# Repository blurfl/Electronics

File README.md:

Maslow PCBs
======================

The TLE5206 offers over-temperature and over-current detection and protection.

This design brings:
- separate controller chip for each motor
- board-mounted heat sinks
- thru-hole parts to aid hand assembly and repair
- mounting holes to match the Arduino Mega2560
- AUX pins on extended end of board
- 4 digital AUX pins
- 2 analog/digital AUX pins
- 3 PWM-capable AUX pins 
- board version ID pins avoids using SPI pins

Layout

Schematic

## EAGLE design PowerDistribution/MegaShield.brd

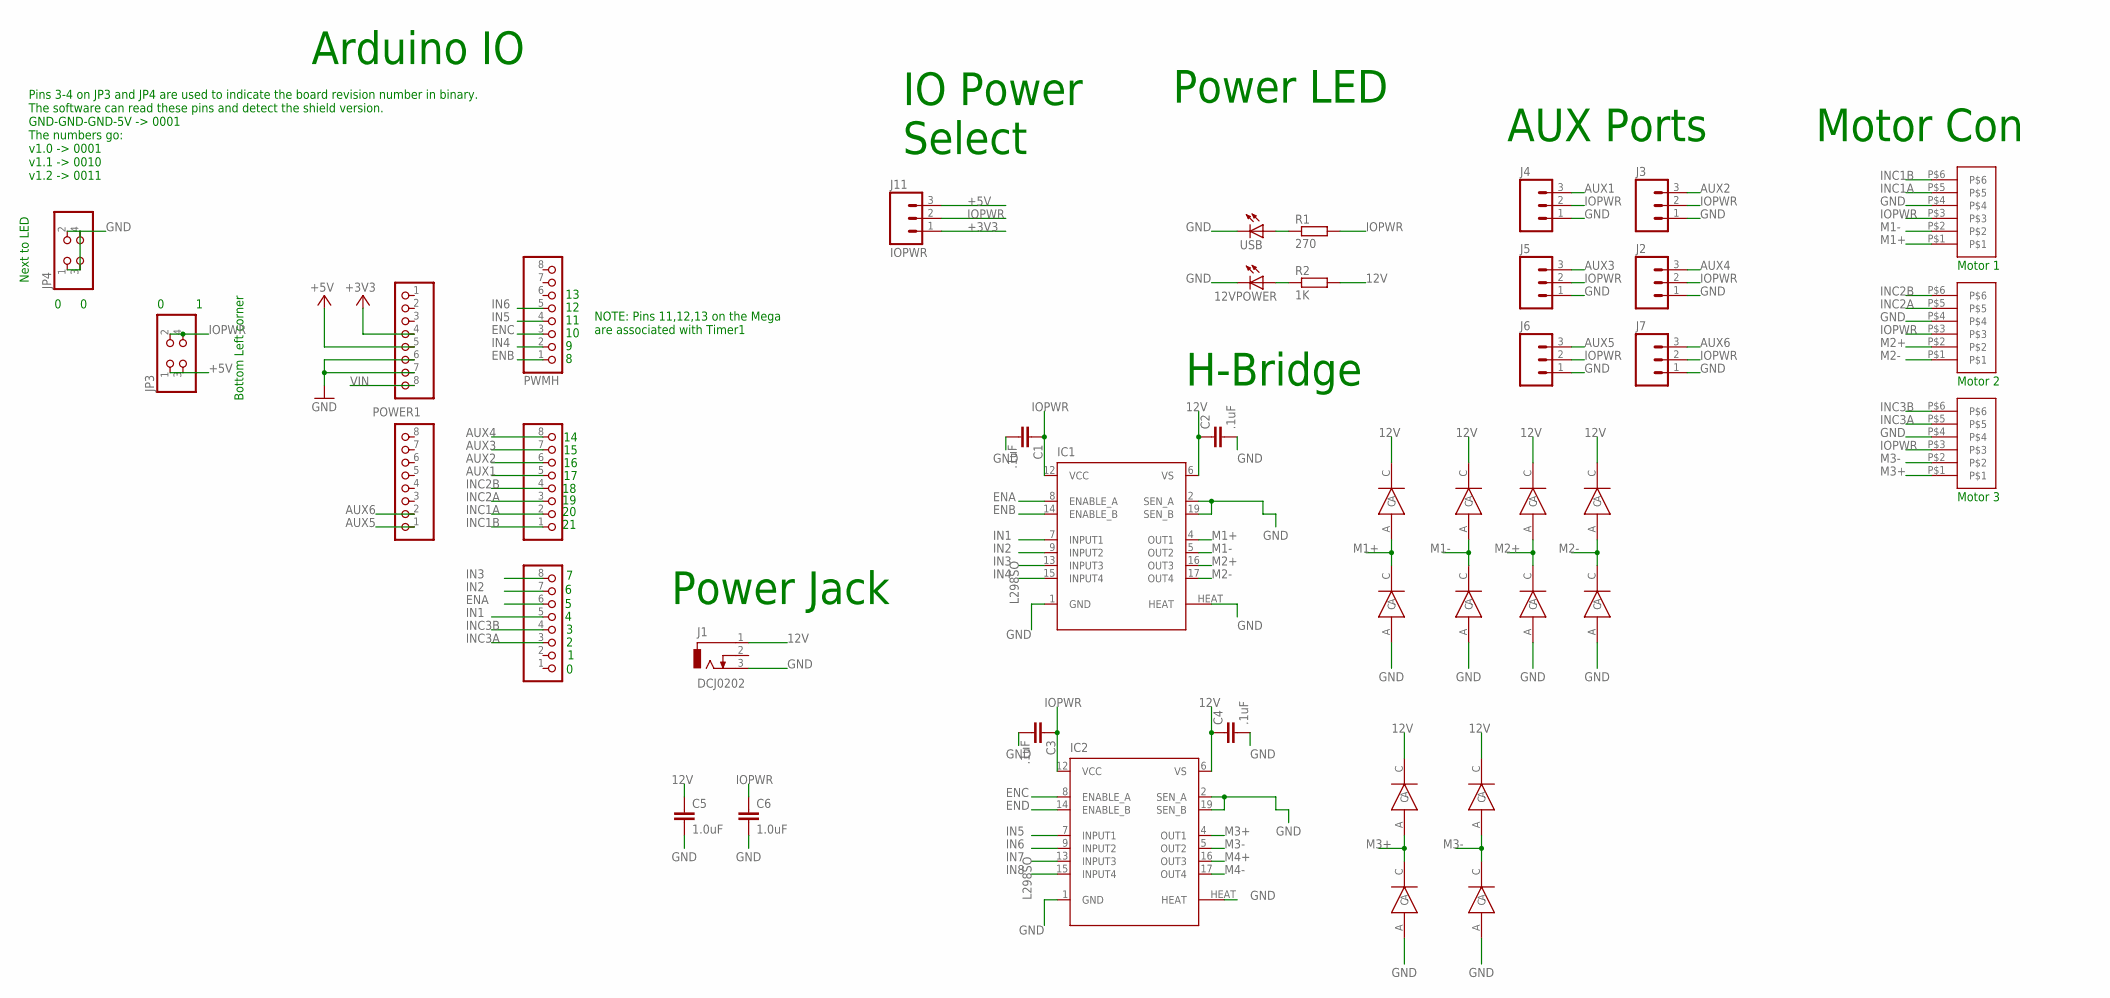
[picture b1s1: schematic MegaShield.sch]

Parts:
12VPOWER: LED_E; LED_1206
C1, C2, C3, C4: .1uF; C0805
C5, C6: 1.0uF; 0805-CAP
COMMUNICATION, COMMUNICATION1: PINHD-1X8; 1X08
IC1, IC2: L298SO; POWERSO-20
J1: DCJ0202
J2, J3, J4, J5, J6, J7: M03LOCK; 1X03_LOCK
J11: IOPWR; 1X03_LOCK
JP3, JP4: PINHD-2X2; 2X02
POWER1: 8x1F-H8.5; 1X08
PWMH: PINHD-1X8; 1X08
PWML: PINHD-1X8; 1X08
R1: 270; R0805
R2: 1K; R0805
U$1, U$12, U$20: JST-PH-6; JST-PHR-6-SMD
U$2, U$3, U$4, U$5, U$6, U$7, U$8, U$9, U$10, U$11, U$13, U$14: MRA4004; SMA
USB: LED_E; LED_1206

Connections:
12V: C2.1, C4.1, C5.1, IC1.6 (VS), IC2.6 (VS), J1.1, R2.2, U$2.C, U$3.C, U$5.C, U$7.C, U$9.C, U$13.C
+3V3: J11.1, POWER1.4
+5V: J11.3, JP3.1, JP3.3, POWER1.5
AUX1: COMMUNICATION.5, J4.3
AUX2: COMMUNICATION.6, J3.3
AUX3: COMMUNICATION.7, J5.3
AUX4: COMMUNICATION.8, J2.3
AUX5: COMMUNICATION1.1, J6.3
AUX6: COMMUNICATION1.2, J7.3
ENA: IC1.8 (ENABLE_A), PWML.6
ENB: IC1.14 (ENABLE_B), PWMH.1
ENC: IC2.8 (ENABLE_A), PWMH.3
END: IC2.14 (ENABLE_B)
GND: 12VPOWER.C, C1.2, C2.2, C3.2, C4.2, C5.2, C6.2, IC1.1 (GND), IC1.2 (SEN_A), IC1.19 (SEN_B), IC1.HEAT, IC2.1 (GND), IC2.2 (SEN_A), IC2.19 (SEN_B), IC2.HEAT, J1.3, J2.1, J3.1, J4.1, J5.1, J6.1, J7.1, JP4.1, JP4.2, JP4.3, JP4.4, POWER1.6, POWER1.7, U$1.P$4, U$4.A, U$6.A, U$8.A, U$10.A, U$11.A, U$12.P$4, U$14.A, U$20.P$4, USB.C
IN1: IC1.7 (INPUT1), PWML.5
IN2: IC1.9 (INPUT2), PWML.7
IN3: IC1.13 (INPUT3), PWML.8
IN4: IC1.15 (INPUT4), PWMH.2
IN5: IC2.7 (INPUT1), PWMH.4
IN6: IC2.9 (INPUT2), PWMH.5
IN7: IC2.13 (INPUT3)
IN8: IC2.15 (INPUT4)
INC1A: COMMUNICATION.2, U$1.P$5
INC1B: COMMUNICATION.1, U$1.P$6
INC2A: COMMUNICATION.3, U$12.P$5
INC2B: COMMUNICATION.4, U$12.P$6
INC3A: PWML.3, U$20.P$5
INC3B: PWML.4, U$20.P$6
IOPWR: C1.1, C3.1, C6.1, IC1.12 (VCC), IC2.12 (VCC), J2.2, J3.2, J4.2, J5.2, J6.2, J7.2, J11.2, JP3.2, JP3.4, R1.2, U$1.P$3, U$12.P$3, U$20.P$3
M1+: IC1.4 (OUT1), U$1.P$1, U$3.A, U$4.C
M1-: IC1.5 (OUT2), U$1.P$2, U$5.A, U$6.C
M2+: IC1.16 (OUT3), U$7.A, U$8.C, U$12.P$2
M2-: IC1.17 (OUT4), U$9.A, U$10.C, U$12.P$1
M3+: IC2.4 (OUT1), U$2.A, U$11.C, U$20.P$1
M3-: IC2.5 (OUT2), U$13.A, U$14.C, U$20.P$2
M4+: IC2.16 (OUT3)
M4-: IC2.17 (OUT4)
unnamed: R1.1, USB.A
unnamed: 12VPOWER.A, R2.1
VIN: POWER1.8

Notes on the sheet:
Motor 1
Motor 2
H-Bridge
Power LED
Power Jack
Arduino IO
AUX Ports
Motor Con
Motor 3
Pins 3-4 on JP3 and JP4 are used to indicate the board revision number in binary. The software can read these pins and detect the shield version. GND-GND-GND-5V -> 0001 The numbers go: v1.0 -> 0001 v1.1 -> 0010 v1.2 -> 0011
NOTE: Pins 11,12,13 on the Mega are associated with Timer1
Next to LED
Bottom Left corner
IO Power Select

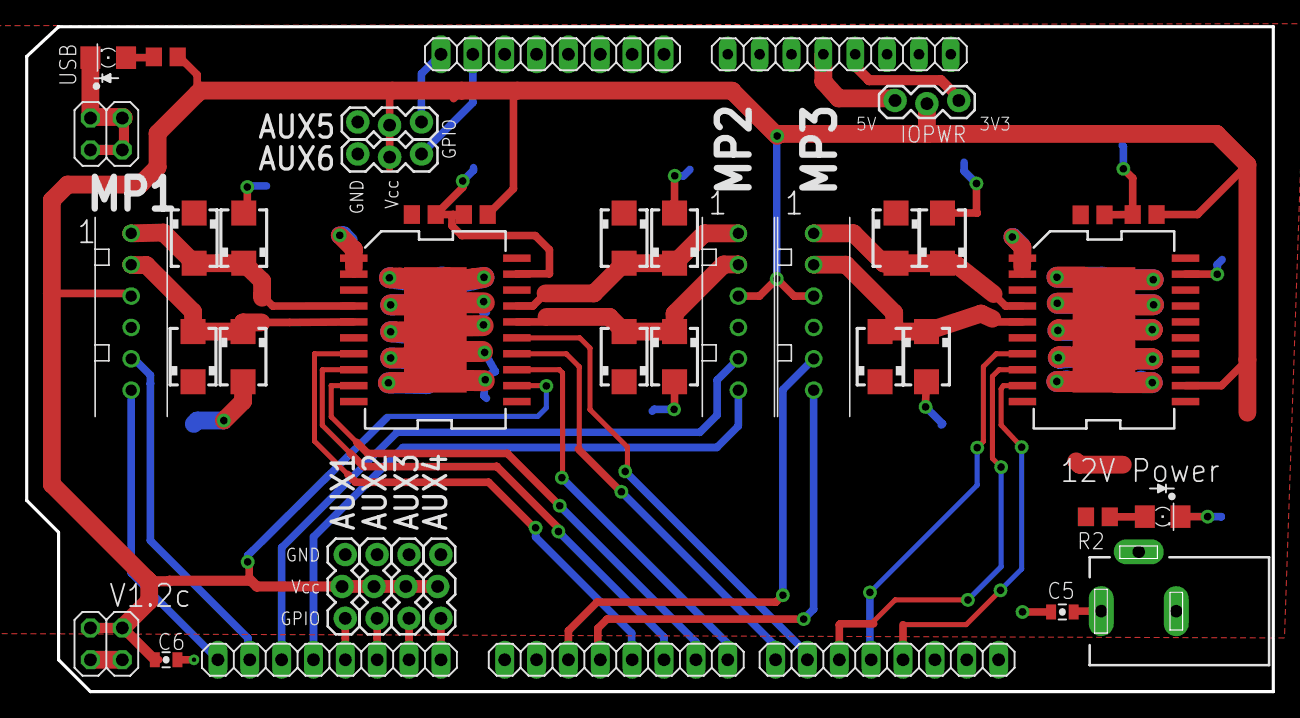
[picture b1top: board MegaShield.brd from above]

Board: 2 copper layers, 99.4 x 53.0 mm, 42 parts (0 on the bottom side), 34 nets.

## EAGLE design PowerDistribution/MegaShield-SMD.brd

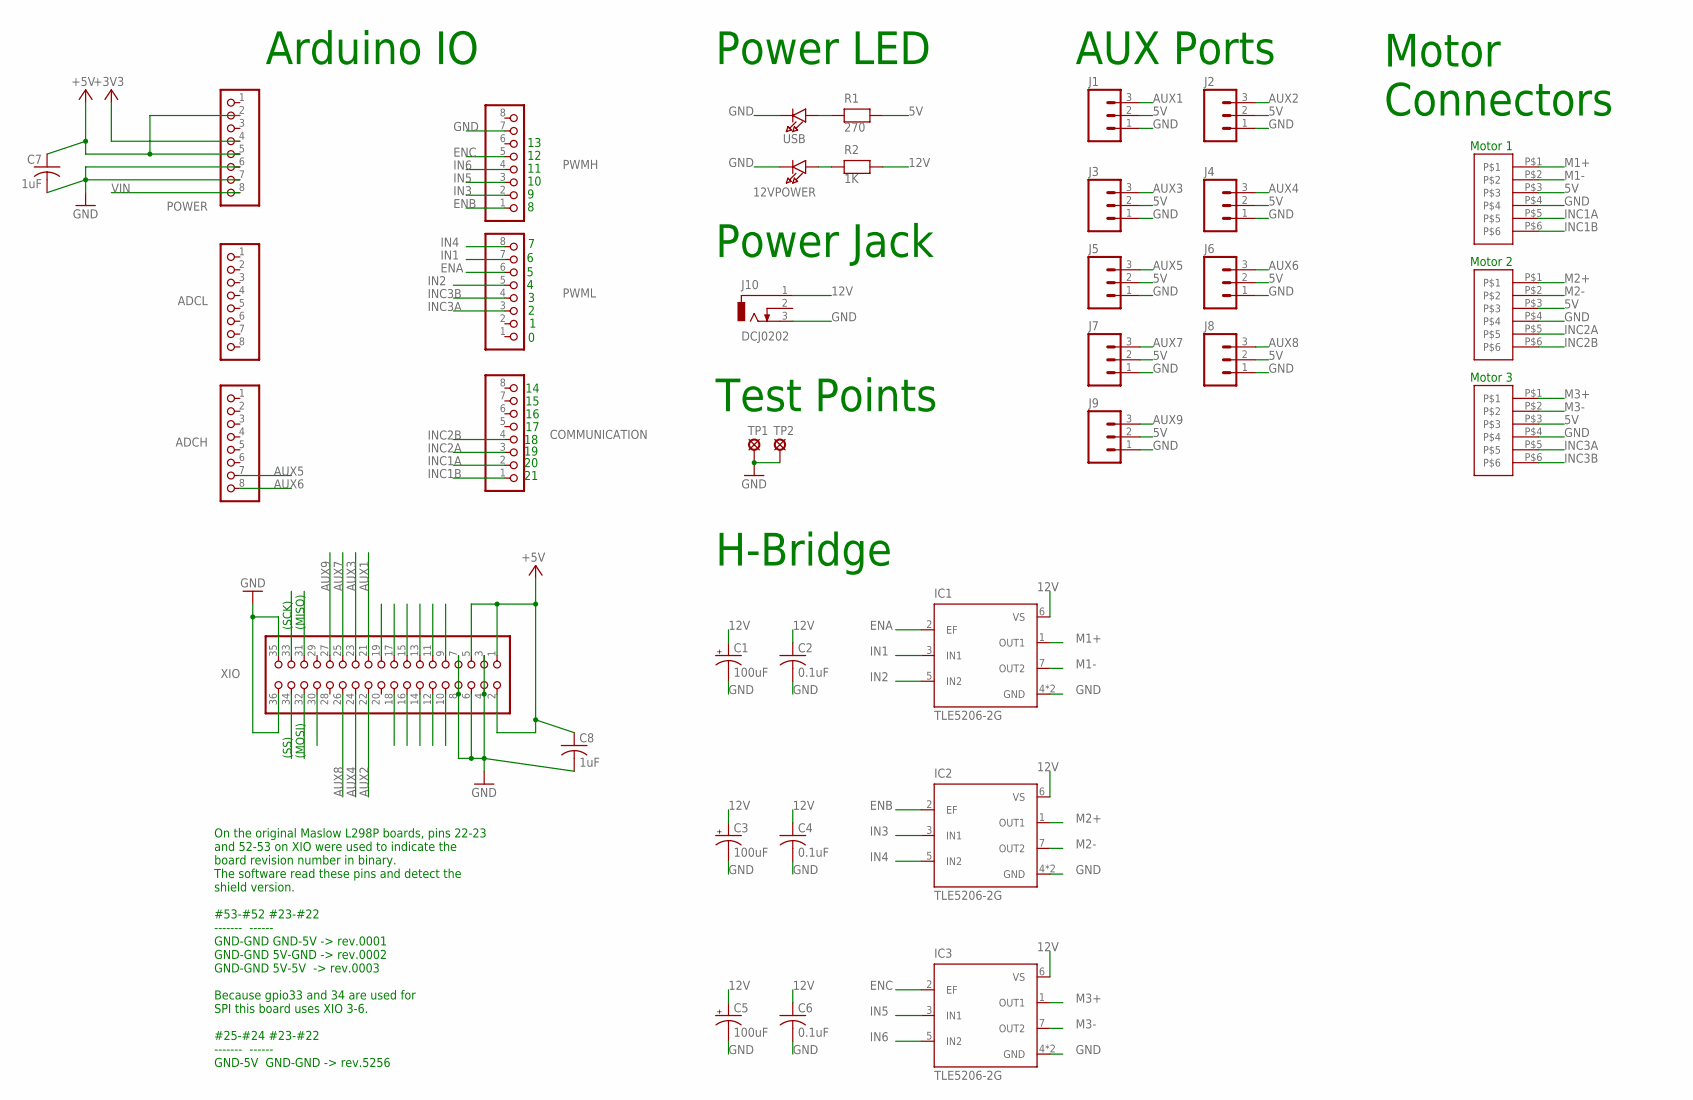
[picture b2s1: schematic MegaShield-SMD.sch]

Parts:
12VPOWER: LED1206; CHIPLED_1206
ADCH: 8x1F-H8.5; 1X08
ADCL: PINHD-1X8; 1X08
C1, C3, C5: 100uF; PANASONIC_E
C2, C4, C6: 0.1uF; C0805K
C7, C8: 1uF; C0805K
COMMUNICATION: PINHD-1X8; 1X08
IC1, IC2: TLE5206-2G; INF-PG-TO263-7-1_L_1PRIMARY
IC3: TLE5206-2G; INF-PG-TO263-7-1_L_1PRIMARY; DIGIKEY TLE5206-2S-ND
J1, J2, J3, J4, J5, J6, J7, J8, J9: M03LOCK; 1X03_LOCK
J10: DCJ0202
MP1, MP2, MP3: JST-PH-6; JST-PHR-6-SMD
POWER: 8x1F-H8.5; 1X08
PWMH: PINHD-1X8; 1X08
PWML: PINHD-1X8; 1X08
R1: 270; 0805
R2: 1K; 0805
TP1, TP2: LSP10
USB: LED1206; CHIPLED_1206
XIO: 18x2F-H8.5; 2X18

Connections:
5V: C7.1, C8.1, J1.2, J2.2, J3.2, J4.2, J5.2, J6.2, J7.2, J8.2, J9.2, MP1.P$3, MP2.P$3, MP3.P$3, POWER.2, POWER.5, R1.2, XIO.1, XIO.2, XIO.5
12V: C1.+, C2.1, C3.+, C4.1, C5.+, C6.1, IC1.6 (VS), IC2.6 (VS), IC3.6 (VS), J10.1, R2.2
+3V3: POWER.4
AUX1: J1.3, XIO.21
AUX2: J2.3, XIO.22
AUX3: J3.3, XIO.23
AUX4: J4.3, XIO.24
AUX5: ADCH.7, J5.3
AUX6: ADCH.8, J6.3
AUX7: J7.3, XIO.25
AUX8: J8.3, XIO.26
AUX9: J9.3, XIO.27
ENA: IC1.2 (EF), PWML.6
ENB: IC2.2 (EF), PWMH.1
ENC: IC3.2 (EF), PWMH.5
GND: 12VPOWER.C, C1.-, C2.2, C3.-, C4.2, C5.-, C6.2, C7.2, C8.2, IC1.4 (GND), IC1.8 (GND), IC2.4 (GND), IC2.8 (GND), IC3.4 (GND), IC3.8 (GND), J1.1, J2.1, J3.1, J4.1, J5.1, J6.1, J7.1, J8.1, J9.1, J10.3, MP1.P$4, MP2.P$4, MP3.P$4, POWER.6, POWER.7, PWMH.7, TP1.MP, TP2.MP, USB.C, XIO.3, XIO.4, XIO.6, XIO.7, XIO.8, XIO.35, XIO.36
IN1: IC1.3 (IN1), PWML.7
IN2: IC1.5 (IN2), PWML.5
IN3: IC2.3 (IN1), PWMH.2
IN4: IC2.5 (IN2), PWML.8
IN5: IC3.3 (IN1), PWMH.3
IN6: IC3.5 (IN2), PWMH.4
INC1A: COMMUNICATION.2, MP1.P$5
INC1B: COMMUNICATION.1, MP1.P$6
INC2A: COMMUNICATION.3, MP2.P$5
INC2B: COMMUNICATION.4, MP2.P$6
INC3A: MP3.P$5, PWML.3
INC3B: MP3.P$6, PWML.4
M1+: IC1.1 (OUT1), MP1.P$1
M1-: IC1.7 (OUT2), MP1.P$2
M2+: IC2.1 (OUT1), MP2.P$1
M2-: IC2.7 (OUT2), MP2.P$2
M3+: IC3.1 (OUT1), MP3.P$1
M3-: IC3.7 (OUT2), MP3.P$2
unnamed: R1.1, USB.A
unnamed: 12VPOWER.A, R2.1
PA6: XIO.9
PA7: XIO.10
PB0: XIO.34
PB1: XIO.33
PB2: XIO.32
PB3: XIO.31
PC0: XIO.18
PC1: XIO.17
PC2: XIO.16
PC3: XIO.15
PC4: XIO.14
PC5: XIO.13
PC6: XIO.12
PC7: XIO.11
PD7: XIO.19
PL0: XIO.30
VIN: POWER.8

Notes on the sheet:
Motor 1
Motor 2
H-Bridge
Power LED
Power Jack
Arduino IO
AUX Ports
Motor Connectors
Motor 3
On the original Maslow L298P boards, pins 22-23 and 52-53 on XIO were used to indicate the board revision number in binary. The software read these pins and detect the shield version. #53-#52 #23-#22 ------- ------ GND-GND GND-5V -> rev.0001 GND-GND 5V-GND -> rev.0002 GND-GND 5V-5V -> rev.0003 Beca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
(SS)
(MOSI)
(SCK)
(MISO)
Test Points

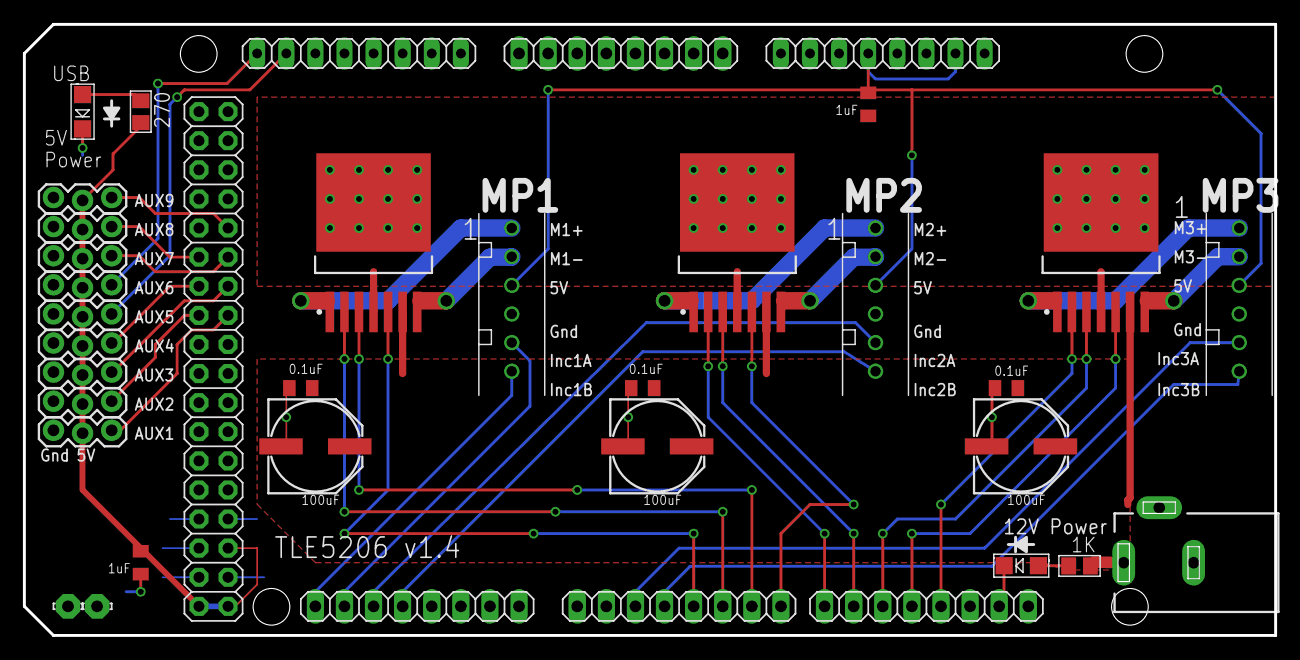
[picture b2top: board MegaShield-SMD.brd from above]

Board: 2 copper layers, 109.2 x 53.3 mm, 37 parts (0 on the bottom side), 35 nets.

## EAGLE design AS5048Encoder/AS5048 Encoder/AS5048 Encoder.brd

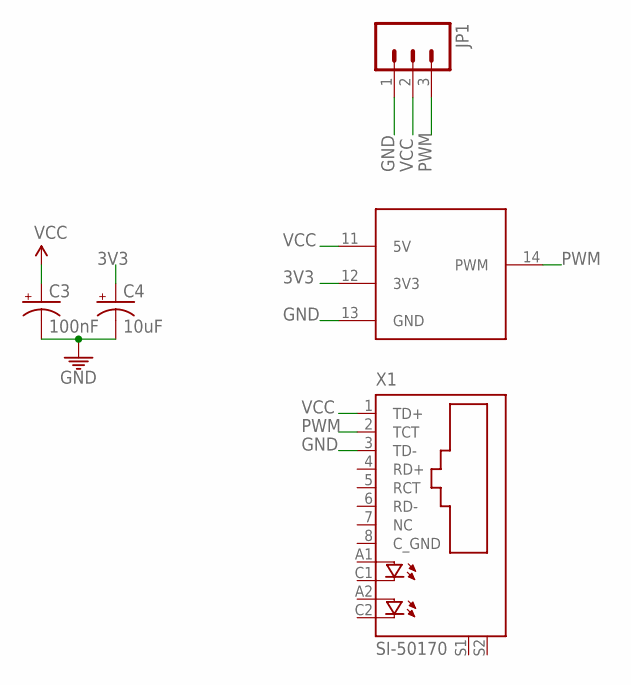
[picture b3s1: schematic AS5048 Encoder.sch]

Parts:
C3: 100nF; EIA3216-KIT
C4: 10uF; EIA3216-KIT
JP1: M03LOCK; 1X03_LOCK
U$1: AS5048; TSOP14
X1: SI-50170

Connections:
3V3: C4.A (+), U$1.12 (3V3)
GND: C3.C (-), C4.C (-), JP1.1, U$1.13 (GND), X1.3 (TD-)
PWM: JP1.3, U$1.14 (PWM), X1.2 (TCT)
VCC: C3.A (+), JP1.2, U$1.11 (5V), X1.1 (TD+)

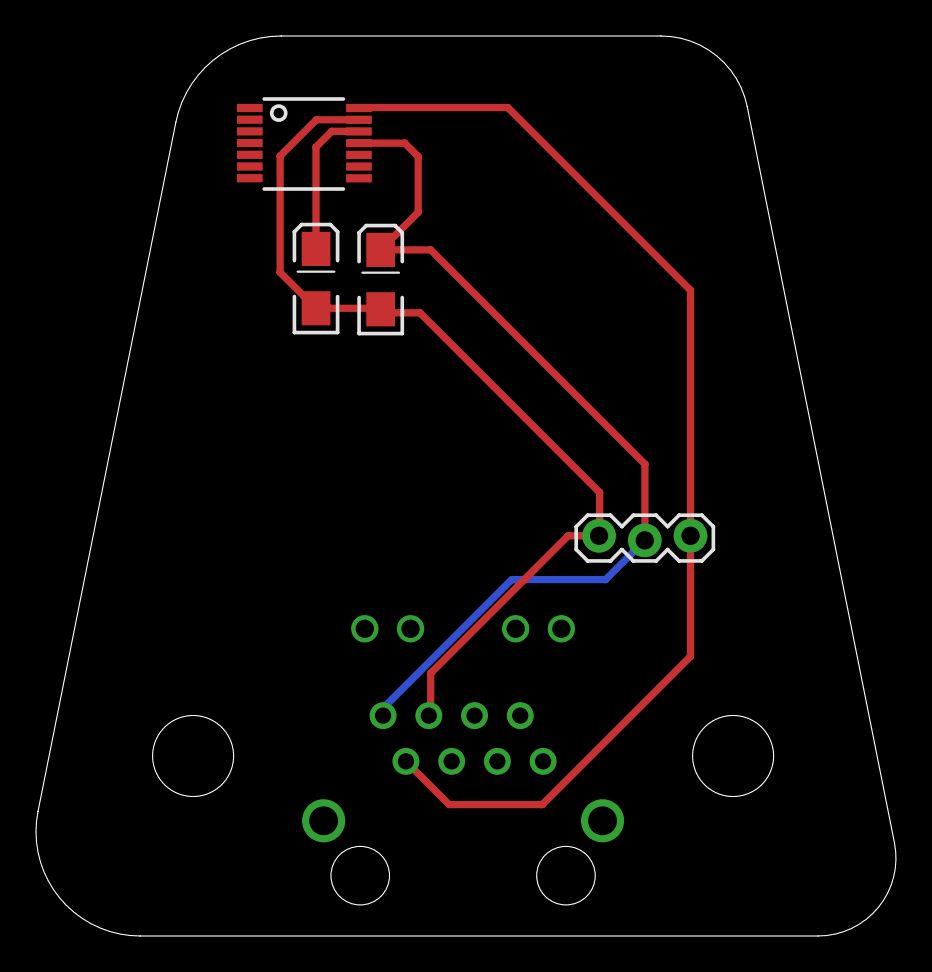
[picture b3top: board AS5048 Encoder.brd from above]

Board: 2 copper layers, 47.8 x 50.0 mm, 5 parts (1 on the bottom side), 4 nets.

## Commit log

2016-07-12 added ethernet jack to docs
2016-07-12 day one end
2016-07-12 real end of day
2016-07-15 pre route
2016-07-15 before rounding corners
2016-07-15 final step before rounding corners
2016-07-15 rounded corners
2016-07-16 moved encoder over
2016-07-16 run cam
2018-01-25 Relplace standard files with Thru-hole files
2018-01-25 Update the images
2018-01-25 Update BOM
2018-01-25 clean up and correct pin spacing
2018-01-26 Add 5V bypass cap
2018-01-26 Move AUX conections to other source pins
2018-01-26 Update PNGs
2018-01-26 Add second 5V bypass cap
2018-01-26 Clean up tPlace layer
    move component values int tPlace layer.
    change board label from TLE520x v1.0 to TLE5206 v1.5
2018-01-26 Add details to README
2018-02-07 Add heatshik fasteners to BOM
2018-02-07 Add SMD version and sepaarate BOMs
2018-02-07 Move caps on schematic, change colors in SMD .brd
2018-03-21 update pictures to include SMD version
2018-04-03 Move Motor Connectors up to avoid Arduino USB connector on MP3
    ... but keep them in line, 'because'.
2019-01-20 Add POWER pins and I/O voltage selector
    Fix board to work with Arduino versions that require 3.3V I/O signals.
2019-01-20 Change version silkscreen from V1.2b to V1.2c

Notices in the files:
parts and their libraries:
SparkFun-Passives: Licensing: CC v3.0 Share-Alike You are welcome to use this library for commercial purposes.
SparkFun-Connectors: Licensing: Creative Commons ShareAlike 4.0 International - https://creativecommons.org/licenses/by-sa/4.0
